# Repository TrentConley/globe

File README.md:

# Travel Globe — Places, remembered.

A visual prototype for a **305 mm (12-inch) programmable travel globe**: charcoal raised terrain, warm gold **visited areas**, and dark places still to explore.

Each saved place contributes an approximate footprint, initially **50 miles in radius**. Nearby footprints merge. No connecting travel lines are drawn, and visiting a city never selects its entire country. The opening example highlights Vancouver while leaving distant Canada and South Dakota dark.

## Engineering prototype A0

Open the [actual CAD assembly](https://trentconley.github.io/globe/engineering.html), [engineering report](https://trentconley.github.io/globe/engineering-report.html), and [downloadable CAD/source package](https://trentconley.github.io/globe/engineering-package.zip).

This release adds a bolted cage, spine, spokes, shell panels, optical baffles, fitted prototype cradle, machining references, wiring/BOM schedules, persistent device software and engineering simulations. The ten-cell optical PCB is routed and reports zero DRC violations/unconnected items; its candidate LED still needs supplier and physical qualification.

**The full globe is not fabrication-ready.** Its six dense matrix board types remain incompletely routed, the south-polar coverage needs revision, and real optics, joint strength, temperatures, supplier fit and hardware operation have not been tested. The 3D assembly uses actual checked meshes; its materials do not predict measured light output. The $4,500 allocation is an unquoted budget ceiling.

Start with the [sample manufacturing plan](https://trentconley.github.io/globe/sample-plan.html), with separate printer/PCB quote packs and clear-versus-tinted controls. The previous [structural concept](https://trentconley.github.io/globe/structure.html) and [early test guide](https://trentconley.github.io/globe/build-guide.html) remain available as historical studies; their counts and mechanics are superseded by A0.

The current **sample A1** adds grid mounting clearance, 1–4.75 mm finish coupons and hardened bench firmware. Its [component/material review](https://trentconley.github.io/globe/sample-qualification.html) lists specific proposed resin/finish products and the unresolved LED/printer approvals. These are review packs, not confirmed supplier orders. The older full-globe A0 package is unchanged.

**Sample fabrication hold:** a conservative 0.20 mm solder envelope over the LED pads leaves only 0.0127 mm to the grid. Obtain actual assembled package/fillet dimensions and tolerances, then relieve the grid if required before fabrication. The passing LED-body clearance check does not qualify solder fit.

## Open and use

Open [the public simulator](https://trentconley.github.io/globe/) in a modern browser, or use `dist/globe.html` locally. The renderer, coastline, and elevation data are bundled into this self-contained file. Some phone file viewers block HTML; the local-server option below is an alternative.

- Add a place by latitude/longitude, or pick its coordinates with **Add on globe**.
- Adjust **Approximate visit radius** to balance recognition and physical display resolution.
- Try **Overlapping Bay Area visits** to see nearby footprints merge, or **Scattered western visits** to see gaps remain dark. These are illustrative examples, not claims about your travel history.
- **Keep highlights on land** clips the visual footprints to the simplified coastline. Turn it off to see the full footprint. This does not promise that the hardware can resolve every coastal edge.
- Use **Print section** to inspect a curved section of the full-size globe and export a shell STL in millimetres. The geography is fixed; changing your visited places changes the light, not the print.
- Compare the ideal coverage with **Show coarse 72-LED approximation** before buying hardware. The cheap test layout can enlarge, shift, or merge small areas.
- Export travel JSON as a backup. Browser storage retains visits locally; it is not the future controller's nonvolatile storage.

On a 305 mm globe, a 50-mile radius is **1.93 mm**, making one footprint about **3.85 mm across**. Zoom in to inspect small areas; the simulator does not artificially enlarge them in the ideal view.

## Build and run

With Node 20+:

```sh
cd /workspace/globe
npm ci
npm run build
npm test
```

Optional local server: `npm start` serves `dist` on port 4173. A phone on the same local network can use the computer's LAN address and port. This development server has no authentication; stop it when finished.

## Saved history

New exports use `{ "version": 2, "radiusMiles": 50, "visits": [{ "name": "Vancouver", "lat": 49.2827, "lon": -123.1207 }] }`.

The simulator accepts earlier version 1 travel files and retains their place coordinates, ignoring old connection flags. Existing personal browser history is migrated to a new storage key, while the original version 1 entry is preserved. The earlier illustrative route demo is replaced by the Vancouver example.

## What the preview and print represent

- Real simplified coastlines and **ETOPO-derived elevation**, showing major ranges with adjustable vertical exaggeration. The preview and STL use the same elevation field.
- Nominal diameter 305 mm before relief. Default 25× exaggeration raises the highest sampled terrain about 3.73 mm; the 40× setting reaches about 5.96 mm. Individual peaks are averaged by the coarse grid.
- Exported curved section: 36° × 36°, about 95 mm across, with at least a 1 mm radial base wall.
- Terrain stays fixed. There are no visit-specific grooves or engraved paths in the print.
- STL contains shape only, without color, lighting, tint, support structures, or printer settings. The simulator’s stand is illustrative; use the separate A0 CAD assembly for the engineered stand.

See [terrain data and scale](docs/elevation.md), [the physical prototype guide](docs/prototype.md), [design decisions](docs/design.md), and [validation record](docs/validation.md). The physical finish, lighting, electronics, and physical phone-to-controller operation remain to be tested.

Coastlines are public-domain [Natural Earth land data](https://github.com/nvkelso/natural-earth-vector/blob/master/geojson/ne_110m_land.geojson); see [provenance](docs/sources.md). Rendering uses Three.js (MIT).

## Reproduce engineering work

Read [cloud/local setup](docs/cloud-setup.md). `tools/build-design.sh` regenerates mechanical geometry, geographic mappings, simulations and assembly assets. `--step` adds slow faceted cage STEP checks. Run `python3 tools/build-report.py` after generating screenshots to render the illustrated report. `tools/package-engineering.py` produces the release archives and checksum manifest.

`npm test` covers the appearance/terrain geometry. `python3 -m unittest discover -s tests -p 'test_firmware.py' -v` covers persistence, protocols and simulated controllers. [Pi installation](firmware/install/README.md) includes a desktop simulation and the proposed hardware provisioning flow.

Generated large CAD/build outputs are excluded from source Git; the public package contains the checked release artifacts. Full matrix candidates are explicitly held, and full-globe Gerbers are not supplied. Hardware/data license notices are in [third-party notices](docs/third-party/hardware-and-data.md).

To reproduce sample A1 after the saved A0 CAD is available: run `python3 cad/sample-readiness.py`, then `python3 tools/check-sample-fit.py`. The latter exports the revised sample viewer mesh and checks both shells against the actual passive-board placement. Run `python3 tools/check-bench-runtime.py --micropython /path/to/micropython` using MicroPython v1.26.0 Unix; the GPIO/timing are mocked. See `engineering/release/sample-*-checks.json` for hashes, assumptions and results. Generate the review packs with `python3 tools/prepare-sample-order.py`, render their combined PDF with `node tools/render-sample-plan.cjs`, then run the pack script again to include the current PDF. Copy `artifacts/assembly/prototype.glb` into `dist/assembly/` after a general A0 assembly build, which otherwise restores the old prototype viewer mesh.

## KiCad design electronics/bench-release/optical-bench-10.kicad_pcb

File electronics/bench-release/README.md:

# Ten-cell optical qualification PCB — A0

This is the routed, DRC-clean passive board for the type-02 curved prototype. It is **not** one of the full-globe matrix boards. Supplier review of the candidate LED datasheet, pad-1 cathode orientation, package dimensions and placement rotation remains required before assembly. No hardware has been tested.

Fabrication: 2 layers, 1.0 mm FR4, 35 µm nominal copper, ordinary lead-free finish, black soldermask preferred, no impedance control. Minimum design track 0.15 mm, copper clearance 0.25 mm, via drill 0.30 mm. Outline and three nonplated 2.2 mm mounting holes are in the Gerber/drill set. Use the actual placement CSV and embedded board footprints as the source of component centers/orientations; front and back assembly are required. D1–D10 are LEDs on the front, R1–R10 are 1 kohm resistors on the rear. P0–P9 and GND are wire pads, not placed parts.

`gerbers/` includes copper, soldermask, paste, silkscreen, board edge, and separate plated/nonplated drill files. The PDF drill maps are inspection aids. `optical-bench-10.kicad_pcb` is the checked source board; `placement.csv`, `bom.csv`, `validation.json` and the DRC JSON support assembler review. Footprints are embedded in the board. The small custom library and fp-lib-table are supplied for editing.

Each GPIO pad drives exactly one series 1 kohm resistor and one LED anode; all cathodes connect to GND. Connect pad N to Pico GPN for N=0–9 and connect common ground. Never apply 12 V. Use firmware/ten-cell-bench and the physical assembly sequence in docs/engineering-report.md. Start at low PWM; qualify finish transmission, optical leakage and mechanical fit before scaling the design.

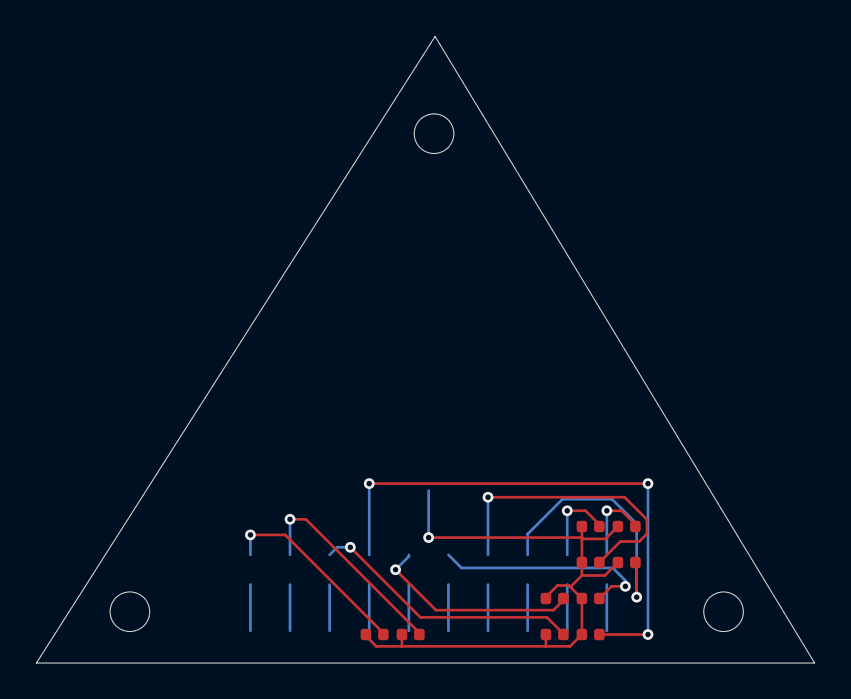
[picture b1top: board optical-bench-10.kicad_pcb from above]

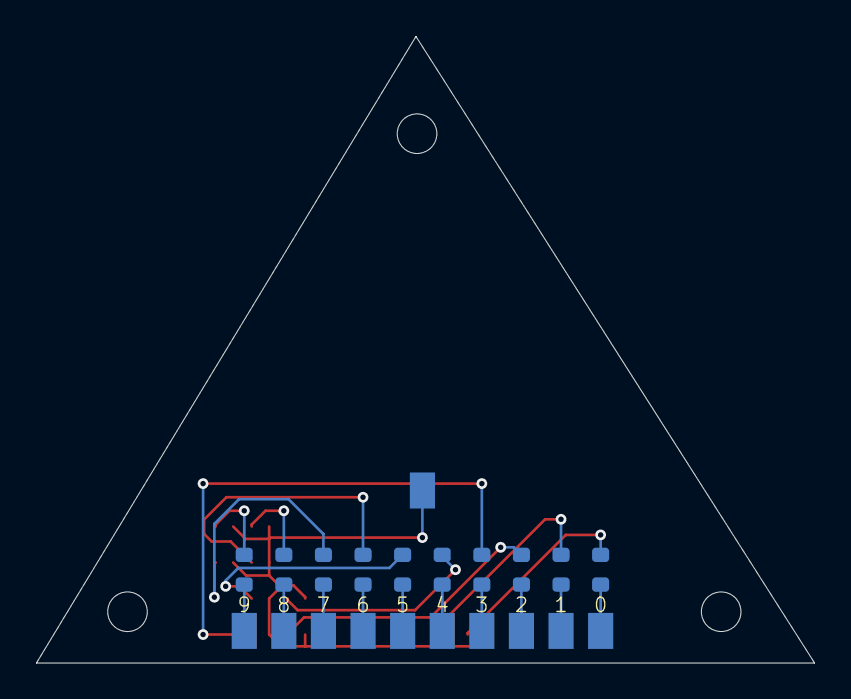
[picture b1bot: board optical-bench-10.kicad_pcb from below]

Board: 2 copper layers, 43.2 x 34.8 mm, 34 parts (21 on the bottom side), 21 nets.

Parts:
D1, D2, D3, D4, D5, D6, D7, D8, D9, D10: Amber 590nm 1005; LED_SMD__LED_0402_1005Metric
GND: GND; WirePad_1.4x2
H1, H2, H3: M2 clearance; MountingHole__MountingHole_2.2mm_M2
P0: P0; WirePad_1.4x2
P1: P1; WirePad_1.4x2
P2: P2; WirePad_1.4x2
P3: P3; WirePad_1.4x2
P4: P4; WirePad_1.4x2
P5: P5; WirePad_1.4x2
P6: P6; WirePad_1.4x2
P7: P7; WirePad_1.4x2
P8: P8; WirePad_1.4x2
P9: P9; WirePad_1.4x2
R1, R2, R3, R4, R5, R6, R7, R8, R9, R10: 1k 1%; Resistor_SMD__R_0603_1608Metric

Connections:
GND: D1.1, D2.1, D3.1, D4.1, D5.1, D6.1, D7.1, D8.1, D9.1, D10.1, GND.1
GPIO0: P0.1, R1.1
GPIO1: P1.1, R2.1
GPIO2: P2.1, R3.1
GPIO3: P3.1, R4.1
GPIO4: P4.1, R5.1
GPIO5: P5.1, R6.1
GPIO6: P6.1, R7.1
GPIO7: P7.1, R8.1
GPIO8: P8.1, R9.1
GPIO9: P9.1, R10.1
LED0: D1.2, R1.2
LED1: D2.2, R2.2
LED2: D3.2, R3.2
LED3: D4.2, R4.2
LED4: D5.2, R5.2
LED5: D6.2, R6.2
LED6: D7.2, R7.2
LED7: D8.2, R8.2
LED8: D9.2, R9.2
LED9: D10.2, R10.2
